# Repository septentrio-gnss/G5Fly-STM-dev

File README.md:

<div align="center">

# G5Fly STM

**Open-source Septentrio GNSS board for FPV drones.**

[Features](#why-g5fly-stm-on-your-drone) •
[Getting started](#getting-started-on-an-fpv-drone) •
[Antenna](#antenna) •
[Production](#production-and-manufacturing) •
[Design guide](DESIGN.md) •
[License](#license)

</div>

G5Fly STM puts a Septentrio Mosaic-G5 GNSS receiver on a 30.5 x 30.5 mm FPV stack board. It mounts directly in your drone's stack and connects to your ArduPilot flight controller over DroneCAN or UART. An STM32G473 runs the AP_Periph firmware on board.

This repository contains the hardware design (KiCad), the production files and the AP_Periph firmware configuration.

Author: <a href="https://github.com/TheophileRaimbault">Théophile Raimbault</a><br>
Contributors: <a href="https://github.com/amelaille">Amélie Hidalgo Peryllous</a>, <a href="https://github.com/robbe2000martens">Robbe Martens</a><br>
Maintainer: Septentrio GNSS GitHub user <githubuser@septentrio.com><br>
License: <a href="https://creativecommons.org/licenses/by-sa/4.0/">Creative Commons Attribution-ShareAlike 4.0</a> and <a href="https://www.oshwa.org/definition/">Open Source Hardware</a><br>

<table>
  <tr>
    <td align="center"><br><strong>Top</strong></td>
    <td align="center"><br><strong>Bottom</strong></td>
  </tr>
</table>

<p align="center">
  <br>
  <em>G5Fly STM mounted in a 30.5 x 30.5 mm FPV stack</em>
</p>

<details>
<summary><strong>Table of contents</strong></summary>

- [Why G5Fly STM on your drone?](#why-g5fly-stm-on-your-drone)
- [Who is this repository for?](#who-is-this-repository-for)
- [Getting started on an FPV drone](#getting-started-on-an-fpv-drone)
  - [Interfaces](#interfaces)
- [Antenna](#antenna)
  - [Recommended antennas](#recommended-antennas)
- [Also compatible with the NXP MR-MCXN-T1 hub](#also-compatible-with-the-nxp-mr-mcxn-t1-hub)
- [Production and manufacturing](#production-and-manufacturing)
  - [JLCPCB requirements](#jlcpcb-requirements)
- [For designers and contributors](#for-designers-and-contributors)
- [Repository structure](#repository-structure)
- [License](#license)

</details>

## Why G5Fly STM on your drone?

- **Fits your FPV stack**: 30.5 x 30.5 mm mounting pattern, stacks directly with standard flight controllers and ESCs
- **Septentrio Mosaic-G5 accuracy**: multi-constellation, multi-frequency GNSS
- **Plug-and-play with ArduPilot**: AP_Periph node with DroneCAN support
- **Drone-standard connectors**: JST-GH connectors for DroneCAN, UART and I2C
- **Flexible antenna power**: 3.3 V or 5 V active antenna supply, selected with a jumper
- **Fully open source**: schematics, PCB, BOM and firmware configuration

## Who is this repository for?

- **Drone builders** who want to buy, assemble or fly the board as-is: start with the sections below.
- **Designers** who want to understand the hardware or make a custom version: go to [DESIGN.md](DESIGN.md).

## Getting started on an FPV drone

1. **Get a board**: build it from the production files in [hardware/versions/v1/kicad/production](hardware/versions/v1/kicad/production/) (see [Production and manufacturing](#production-and-manufacturing)).
2. **Set the antenna voltage**: solder `JP1` according to your antenna (see [Antenna](#antenna)).
3. **Flash the firmware**: build and flash AP_Periph using the configuration in [firmware](firmware/).
4. **Mount it in the stack**: install the board on the 30.5 x 30.5 mm pattern.
5. **Wire it to the flight controller**: use DroneCAN (recommended) or UART, then power it from the 5 V supply of the stack or via USB on the bench.
6. **Configure ArduPilot**: enable the DroneCAN GPS in Mission Planner (see [firmware/README.md](firmware/README.md)).
7. **Check before flying**: verify the status LEDs and wait for a valid GNSS fix outdoors.

### Interfaces

- **DroneCAN**: recommended link to the flight controller
- **UART**: direct serial link to the flight controller or a companion computer
- **I2C**: for external sensors
- **USB**: power and configuration on the bench
- **Reset input and status LEDs**

## Antenna

- Use an active antenna only with the voltage specified by the antenna manufacturer.
- Check the antenna connector and the `JP1` configuration before powering the board.
- On the drone, route the antenna cable away from the VTX, ESCs and motor wires, and mount the antenna with a clear view of the sky.

<div style="background-color:#ffebee; border-left:5px solid #c62828; padding:10px; border-radius:5px; margin:10px 0;">
  <strong>Warning:</strong> Solder <code>JP1</code> before using an active antenna. If the jumper is left open, the <code>VANT</code> net is not powered and the antenna may not work, causing a significant loss of GNSS performance. Select only one voltage according to the antenna datasheet.
</div>

<table>
  <tr>
    <td align="center"><br><strong>3.3 V antenna</strong><br>Connect <code>VANT</code> to <code>+3.3V_RF</code>.</td>
    <td align="center"><br><strong>5 V antenna</strong><br>Connect <code>VANT</code> to <code>+5V</code>.</td>
  </tr>
</table>

### Recommended antennas

- D-Helix HX-CHX600A
- D-Helix HX-CH7609A
- Calian HC990EXF

An SMA-to-MMCX adapter is often needed to connect these antennas to the board.

## Also compatible with the NXP MR-MCXN-T1 hub

G5Fly STM is designed for FPV drones first, but it also works with the NXP MR-MCXN-T1 hub through its DF40 connector.

<table>
  <tr>
    <td align="center"><br><strong>MR-MCXN-T1 housing</strong></td>
    <td align="center"><br><strong>DF40 connector</strong></td>
  </tr>
</table>

The DF40 connector carries the GNSS UART, the PPS and Event A signals, and the 5 V supply from the hub.

To get started on the hub, see the [G5Fly NXP repository](https://github.com/septentrio-gnss/G5Fly-NXP). It provides a Zephyr test application for the MR-MCXN-T1 that reads the GNSS position over NMEA, measures the PPS, and sends Event A pulses.

For an overview of the hardware and software integration, see the [MR-MCXN-T1 integration slides](resources/mr-mcxn-t1/NXP%20integration%20HW-FW.pdf).

## Production and manufacturing

For a production build without hardware changes:

- Use the KiCad project and manufacturing files in [hardware/versions/v1/kicad](hardware/versions/v1/kicad/).
- Provide the manufacturer with the schematic, PCB files, BOM and CPL.
- Check the antenna connector type, jumper configuration and power options before assembly.

### JLCPCB requirements

- Keep the default KiCad PCB setup and its calculated impedance settings.
- Manufacture the board as a 6-layer PCB.
- `PCB Requirement: User.1 layer should be used as the V-cut guide layer.`
- Follow the PCB design rules in [hardware/common/design_rules/design-rules.md](hardware/common/design_rules/design-rules.md).
- Use the [G5Fly_STM_v1 production archive](hardware/versions/v1/kicad/production/G5Fly_STM_v1.zip), prepared for JLCPCB.

## For designers and contributors

The detailed hardware design guide is in [DESIGN.md](DESIGN.md). It covers:

- Overall architecture and major blocks
- Component selection and board organization
- How to create a custom derivative board
- Manufacturing and validation recommendations
- AP_Periph firmware configuration and DroneCAN bring-up

Useful resources:

- STM32 schematic: [resources/schematics/G5FLY_STM_schematics.pdf](resources/schematics/G5FLY_STM_schematics.pdf)
- Block diagram: [resources/schematics/G5Fly_STM32_drawio.png](resources/schematics/G5Fly_STM32_drawio.png)
- Contribution rules: [GUIDELINES.md](GUIDELINES.md) and [VERSIONING.md](VERSIONING.md)

## Repository structure

- [hardware](hardware): KiCad projects, libraries, 3D models, design rules and production files
- [firmware](firmware): AP_Periph configuration (`hwdef.dat`, `defaults.parm`)
- [resources](resources): photos, marketing visuals, schematics and MR-MCXN-T1 integration documents

## License

The G5Fly hardware design files (schematics, PCB layouts, production files) and documentation are released under the [Creative Commons Attribution-ShareAlike 4.0 International License](https://creativecommons.org/licenses/by-sa/4.0/) (CC BY-SA 4.0). See the [LICENSE](LICENSE) file for the full text.

You are free to share and adapt this design, including for commercial purposes, as long as you:
- **give appropriate credit** to Septentrio and the original authors,
- **indicate if changes were made**,
- **distribute your derivatives under the same license**.

G5Fly is open-source hardware and follows the [Open Source Hardware Definition](https://www.oshwa.org/definition/).

<p align="right"><a href="#g5fly-stm">Back to top ↑</a></p>

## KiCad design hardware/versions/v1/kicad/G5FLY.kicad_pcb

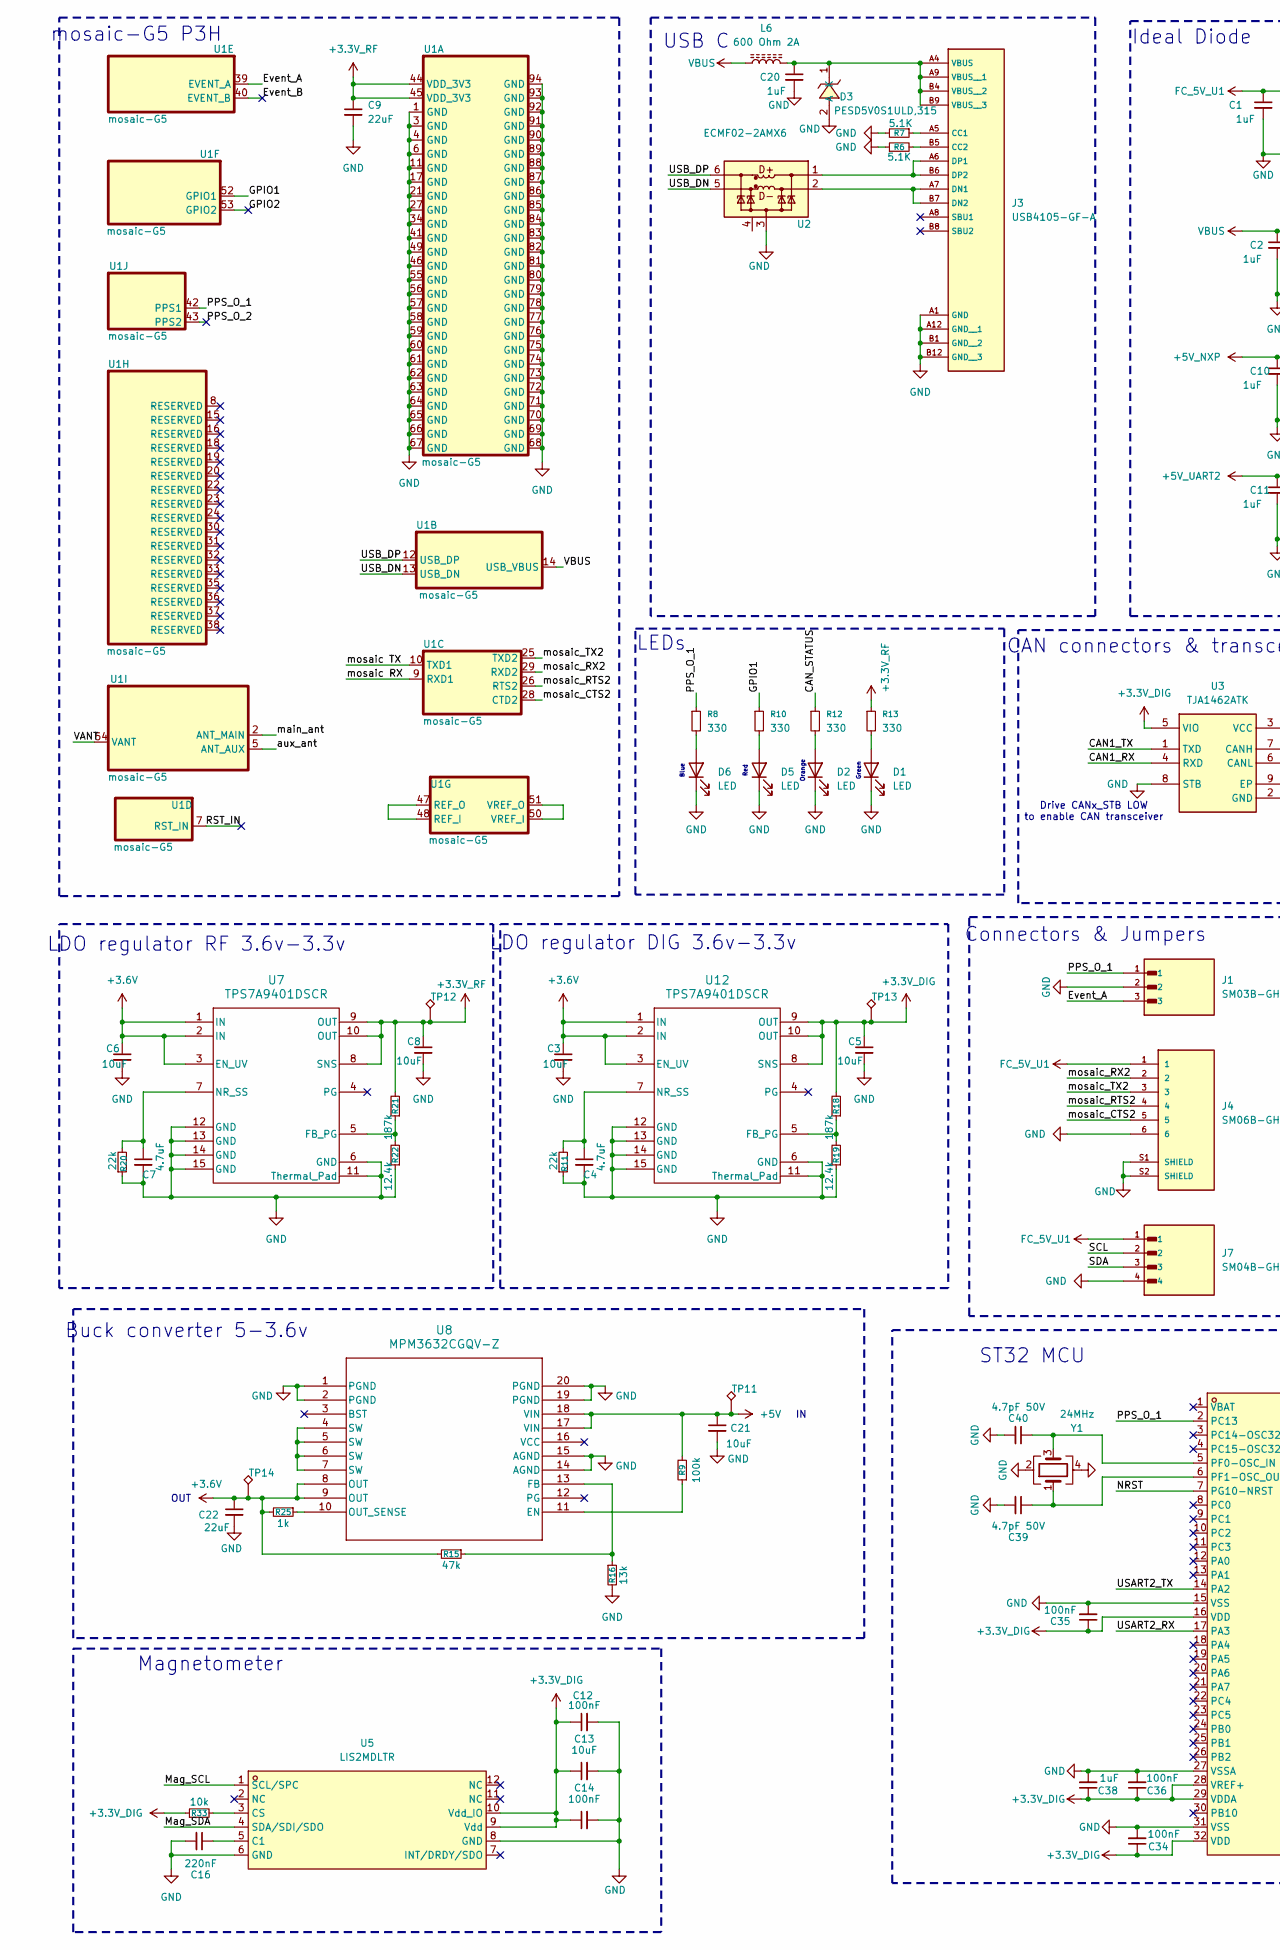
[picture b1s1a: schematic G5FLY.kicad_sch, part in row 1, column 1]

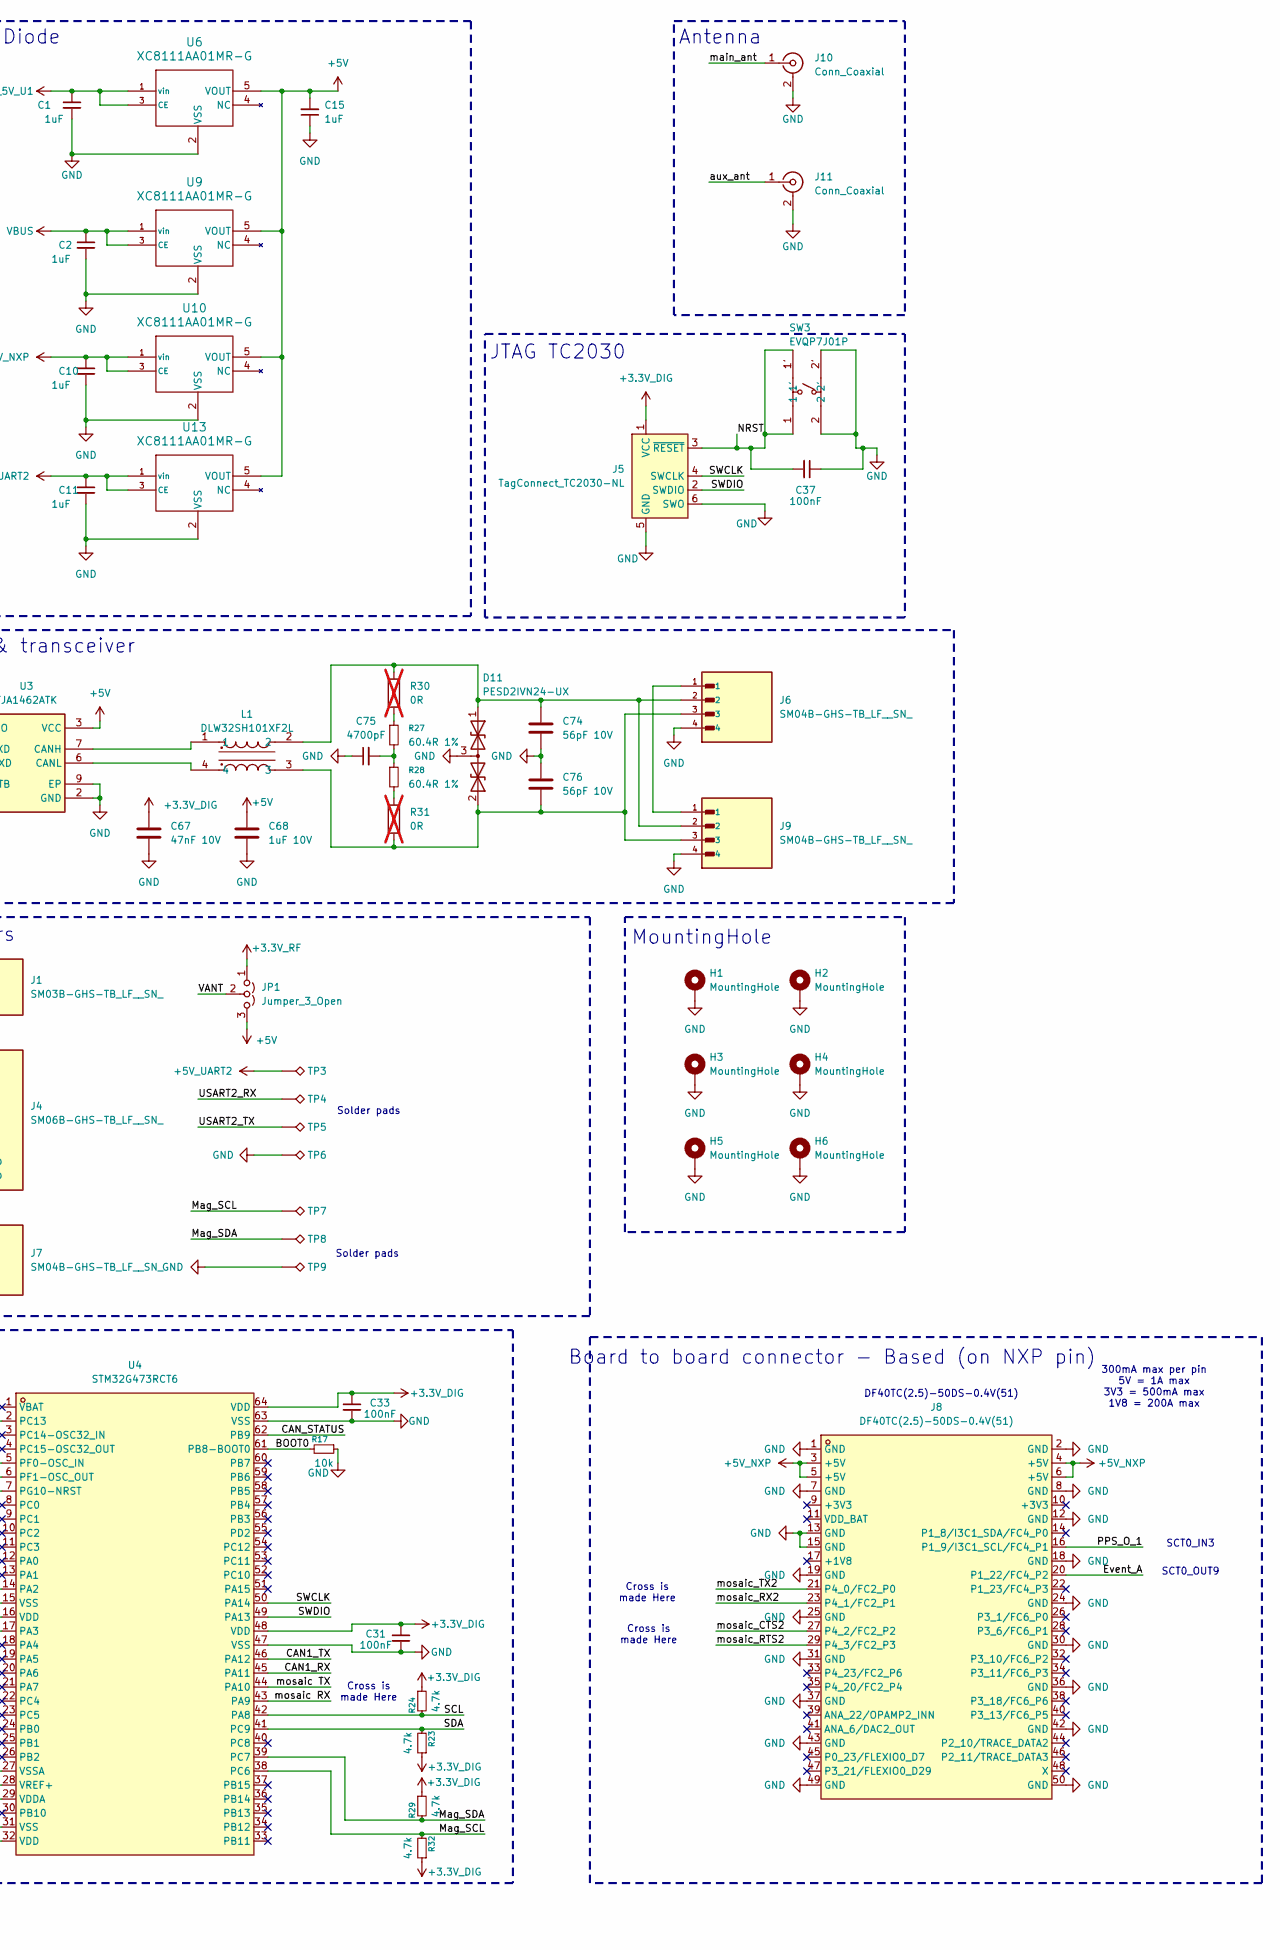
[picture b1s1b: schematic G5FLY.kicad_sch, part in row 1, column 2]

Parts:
C1, C2, C10, C11, C15, C20, C38: 1uF; C_0402_1005Metric
C3, C5, C6, C8, C21: 10uF; C_0603_1608Metric
C4: 4.7uF; C_0402_1005Metric
C7: 4.7uF; C_0603_1608Metric
C9, C22: 22uF; C_0805_2012Metric
C12, C14, C31, C33, C34, C35, C36, C37: 100nF; C_0402_1005Metric
C13: 10uF; C_0402_1005Metric
C16: 220nF; C_0402_1005Metric
C39, C40: 4.7pF 50V; C_0402_1005Metric
C67: 47nF 10V; C_0402_1005Metric; JLCPCB C77012
C68: 1uF 10V; C_0402_1005Metric; JLCPCB C528974
C74, C76: 56pF 10V; C_0402_1005Metric; JLCPCB C107007
C75: 4700pF
D1, D2, D5, D6: LED; LED_0402_1005Metric
D3: PESD5V0S1ULD,315; SOD-882_L1.0-W0.6-RD; MPN PESD5V0S1ULD,315; LCSC Part C552570
D11: PESD2IVN24-UX; SOT-323_SC-70; JLCPCB C552496
H1, H2, H3, H4, H5, H6: MountingHole; MountingHole_3.2mm_M3_DIN965_Pad
J1: SM03B-GHS-TB_LF__SN_; JST_SM03B-GHS-TB_LF__SN_
J3: USB4105-GF-A; USB_C_Receptacle_GCT_USB4105-xx-A_16P_TopMnt_Horizontal
J4: SM06B-GHS-TB_LF__SN_; JST_SM06B-GHS-TB_LF__SN_; PARTREV N/A
J5: TagConnect_TC2030-NL; Tag-Connect_TC2030-IDC-NL_2x03_P1.27mm_Vertical
J6, J7, J9: SM04B-GHS-TB_LF__SN_; JST_SM04B-GHS-TB_LF__SN_
J8: DF40TC(2.5)-50DS-0.4V(51); CONN-SMD_DF40C-50DS-0.4V51; MPN DF40C-50DS-0.4V(51); LCSC Part C424646
J10, J11: Conn_Coaxial; SAMTEC_MMCX-J-P-H-RA-TH1
JP1: Jumper_3_Open; SolderJumper-3_P1.3mm_Open_Pad1.0x1.5mm_NumberLabels
L1: DLW32SH101XF2L; FILTER-SMD_4P-L3.2-W2.5-BL_DLW32SH510XK2L; MPN DLW32SH101XF2L; LCSC Part C1857795
L6: 600 Ohm 2A; L_0603_1608Metric; DigiKey 445-MPZ2012S601ATD25CT-ND
R6, R7: 5.1K; R_0402_1005Metric
R8, R10, R12, R13: 330; R_0402_1005Metric
R9: 100k; R_0402_1005Metric
R11, R20: 22k; R_0402_1005Metric
R15: 47k; R_0402_1005Metric
R16: 13k; R_0402_1005Metric
R17, R33: 10k; R_0402_1005Metric
R18, R21: 187k; R_0402_1005Metric
R19, R22: 12.4k; R_0402_1005Metric
R23, R24, R29, R32: 4.7k; R_0402_1005Metric
R25: 1k; R_0402_1005Metric
R27, R28: 60.4R 1%; R_0402_1005Metric
R30, R31: 0R; R_0603_1608Metric; DigiKey 541-60.4SCT-ND; not fitted
SW3: EVQP7J01P; SW-SMD_EVQP7J01P; MPN EVQP7J01P; LCSC Part C2828254
TP3, TP4, TP5, TP6, TP7, TP8, TP9: TestPoint_Alt; TestPoint_Pad_1.5x1.5mm
TP11, TP12, TP13, TP14: TestPoint_Alt; TestPoint_Pad_D1.0mm
U1: mosaic-G5; LGA54_MOSAIC-MINI_SEP
U2: ECMF02-2AMX6; ST_UQFN-6L_1.5x1.7mm_P0.5mm
U3: TJA1462ATK; SON65P300X300X100-9N-D; JLCPCB C3229259
U4: STM32G473RCT6; LQFP-64_L10.0-W10.0-P0.50-LS12.0-BL; MPN STM32G473RCT6; LCSC Part C529361
U5: LIS2MDLTR; VLGA-12_L2.0-W2.0-P0.50-BL; MPN LIS2MDLTR; LCSC Part C919695
U6, U9, U10, U13: XC8111AA01MR-G; IC_XC8111AA01MR-G
U7, U12: TPS7A9401DSCR; DSC0010J-MFG
U8: MPM3632CGQV-Z; QFN3p0x5p0x1p6_MPM3632C_MNP
Y1: 24MHz; Crystal_SMD_2016-4Pin_2.0x1.6mm; DigiKey 1923-830108212309CT-ND

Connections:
+3.3V_DIG: C5.1, C12.1, C13.1, C14.1, C31.1, C33.1, C34.1, C35.1, C36.1, C38.1, C67.1, J5.1 (VCC), R18.2, R23.1, R24.1, R29.1, R32.1, R33.1, TP13.1 (1_1), U3.5 (VIO), U4.16 (VDD), U4.28 (VREF+), U4.29 (VDDA), U4.32 (VDD), U4.48 (VDD), U4.64 (VDD), U5.9 (Vdd), U5.10 (Vdd_IO), U12.8 (SNS), U12.9 (OUT), U12.10 (OUT)
+3.3V_RF: C8.1, C9.1, JP1.1 (A), R13.1, R21.2, TP12.1 (1_1), U1.44 (VDD_3V3), U1.45 (VDD_3V3), U7.8 (SNS), U7.9 (OUT), U7.10 (OUT)
+3.6V: C3.1, C6.1, C22.1, R15.2, R25.2, TP14.1 (1_1), U7.1 (IN), U7.2 (IN), U7.3 (EN_UV), U8.8 (OUT), U8.9 (OUT), U12.1 (IN), U12.2 (IN), U12.3 (EN_UV)
+5V: C15.2, C21.1, C68.1, JP1.3 (B), R9.2, TP11.1 (1_1), U3.3 (VCC), U6.5 (VOUT), U8.17 (VIN), U8.18 (VIN), U9.5 (VOUT), U10.5 (VOUT), U13.5 (VOUT)
+5V_NXP: C10.1, J8.3 (+5V), J8.4 (+5V), J8.5 (+5V), J8.6 (+5V), U10.1 (vin), U10.3 (CE)
+5V_UART2: C11.1, TP3.1 (1_1), U13.1 (vin), U13.3 (CE)
/BOOT0: R17.2, U4.61 (PB8-BOOT0)
/CAN1_RX: U3.4 (RXD), U4.45 (PA11)
/CAN1_TX: U3.1 (TXD), U4.46 (PA12)
/CAN_STATUS: R12.1, U4.62 (PB9)
/Event_A: J1.3, J8.20 (P1_22/FC4_P2), U1.39 (EVENT_A)
/Event_B: U1.40 (EVENT_B)
/GPIO1: R10.1, U1.52 (GPIO1)
/GPIO2: U1.53 (GPIO2)
/Mag_SCL: R32.2, TP7.1 (1_1), U4.38 (PC6), U5.1 (SCL/SPC)
/Mag_SDA: R29.2, TP8.1 (1_1), U4.39 (PC7), U5.4 (SDA/SDI/SDO)
/NRST: C37.2, J5.3 (~RESET), SW3.1, SW3.1', U4.7 (PG10-NRST)
/PPS_O_1: J1.1, J8.16 (P1_9/I3C1_SCL/FC4_P1), R8.1, U1.42 (PPS1), U4.2 (PC13)
/PPS_O_2: U1.43 (PPS2)
/RST_IN: U1.7 (RST_IN)
/SCL: J7.2, R24.2, U4.42 (PA8)
/SDA: J7.3, R23.2, U4.41 (PC9)
/SWCLK: J5.4 (SWCLK), U4.50 (PA14)
/SWDIO: J5.2 (SWDIO), U4.49 (PA13)
/USART2_RX: TP4.1 (1_1), U4.17 (PA3)
/USART2_TX: TP5.1 (1_1), U4.14 (PA2)
/USB_DN: U1.13 (USB_DN), U2.5 (D-_out)
/USB_DP: U1.12 (USB_DP), U2.6 (D+_out)
/VANT: JP1.2 (C), U1.54 (VANT)
/aux_ant: J11.1 (In), U1.5 (ANT_AUX)
/main_ant: J10.1 (In), U1.2 (ANT_MAIN)
/mosaic RX: U1.9 (RXD1), U4.43 (PA9)
/mosaic TX: U1.10 (TXD1), U4.44 (PA10)
/mosaic_CTS2: J4.5, J8.27 (P4_2/FC2_P2), U1.28 (CTD2)
/mosaic_RTS2: J4.4, J8.29 (P4_3/FC2_P3), U1.26 (RTS2)
/mosaic_RX2: J4.2, J8.23 (P4_1/FC2_P1), U1.29 (RXD2)
/mosaic_TX2: J4.3, J8.21 (P4_0/FC2_P0), U1.25 (TXD2)
FC_5V_U1: C1.1, J4.1, J7.1, U6.1 (vin), U6.3 (CE)
GND: C1.2, C2.2, C3.2, C4.2, C5.2, C6.2, C7.2, C8.2, C9.2, C10.2, C11.2, C12.2, C13.2, C14.2, C15.1, C16.2, C20.2, C21.2, C22.2, C31.2, C33.2, C34.2, C35.2, C36.2, C37.1, C38.2, C39.2, C40.2, C67.2, C68.2, C74.2, C75.1, C76.1, D1.1 (K), D2.1 (K), D3.2 (A), D5.1 (K), D6.1 (K), D11.3 (common), H1.1 (1_1), H2.1 (1_1), H3.1 (1_1), H4.1 (1_1), H5.1 (1_1), H6.1 (1_1), J1.2, J3.A1 (GND), J3.A12 (GND__1), J3.B1 (GND__2), J3.B12 (GND__3), J4.6, J4.S1 (SHIELD), J4.S2 (SHIELD), J5.5 (GND), J5.6 (SWO), J6.4, J7.4, J8.1 (GND), J8.2 (GND), J8.7 (GND), J8.8 (GND), J8.12 (GND), J8.13 (GND), J8.15 (GND), J8.18 (GND), J8.19 (GND), J8.24 (GND), J8.25 (GND), J8.30 (GND), J8.31 (GND), J8.36 (GND), J8.37 (GND), J8.42 (GND), J8.43 (GND), J8.49 (GND), J8.50 (GND), J9.4, J10.2 (Ext), J11.2 (Ext), R6.1, R7.2, R11.1, R16.2, R17.1, R19.1, R20.1, R22.1, SW3.2, SW3.2', TP6.1 (1_1), TP9.1 (1_1), U1.1 (GND), U1.3 (GND), U1.4 (GND), U1.6 (GND), U1.11 (GND), U1.17 (GND), U1.21 (GND), U1.27 (GND), U1.34 (GND), U1.41 (GND), U1.46 (GND), U1.49 (GND), U1.55 (GND), U1.56 (GND), U1.57 (GND), U1.58 (GND), U1.59 (GND), U1.60 (GND), U1.61 (GND), U1.62 (GND), U1.63 (GND), U1.64 (GND), U1.65 (GND), U1.66 (GND), U1.67 (GND), U1.68 (GND), U1.69 (GND), U1.70 (GND), U1.71 (GND), U1.72 (GND), U1.73 (GND), U1.74 (GND), U1.75 (GND), U1.76 (GND), U1.77 (GND), U1.78 (GND), U1.79 (GND), U1.80 (GND), U1.81 (GND), U1.82 (GND), U1.83 (GND), U1.84 (GND), U1.85 (GND), U1.86 (GND), U1.87 (GND), U1.88 (GND), U1.89 (GND), U1.90 (GND), U1.91 (GND), U1.92 (GND), U1.93 (GND), U1.94 (GND), U2.3 (GND), U3.2 (GND), U3.8 (STB), U3.9 (EP), U4.15 (VSS), U4.27 (VSSA), U4.31 (VSS), U4.47 (VSS), U4.63 (VSS), U5.6 (GND), U5.8 (GND), U6.2 (VSS), U7.6 (GND), U7.11 (Thermal_Pad), U7.12 (GND), U7.13 (GND), U7.14 (GND), U7.15 (GND), U8.1 (PGND), U8.2 (PGND), U8.14 (AGND), U8.15 (AGND), U8.19 (PGND), U8.20 (PGND), U9.2 (VSS), U10.2 (VSS), U12.6 (GND), U12.11 (Thermal_Pad), U12.12 (GND), U12.13 (GND), U12.14 (GND), U12.15 (GND), U13.2 (VSS), Y1.2, Y1.4
unnamed: C75.2, R27.2, R28.1
unnamed: D1.2 (A), R13.2
unnamed: D2.2 (A), R12.2
unnamed: C20.1, D3.1 (K), J3.A4 (VBUS), J3.A9 (VBUS__1), J3.B4 (VBUS__2), J3.B9 (VBUS__3), L6.2
unnamed: D5.2 (A), R10.2
unnamed: D6.2 (A), R8.2
unnamed: C74.1, D11.1 (A1), J6.2, J9.2, L1.2, R30.1
unnamed: C76.2, D11.2 (A2), J6.3, J9.3, L1.3, R31.2
unnamed: J3.A5 (CC1), R7.1
unnamed: J3.B5 (CC2), R6.2
unnamed: J3.A7 (DN1), J3.B7 (DN2), U2.2 (D-_in)
unnamed: J3.A6 (DP1), J3.B6 (DP2), U2.1 (D+_in)
unnamed: J6.1, J9.1
unnamed: R27.1, R30.2
unnamed: R28.2, R31.1
unnamed: U1.47 (REF_O), U1.48 (REF_I)
unnamed: U1.50 (VREF_I), U1.51 (VREF_O)
unnamed: L1.1, U3.7 (CANH)
unnamed: L1.4, U3.6 (CANL)
unnamed: C40.1, U4.5 (PF0-OSC_IN), Y1.3
unnamed: C39.1, U4.6 (PF1-OSC_OUT), Y1.1
unnamed: C16.1, U5.5 (C1)
unnamed: R33.2, U5.3 (CS)
unnamed: R21.1, R22.2, U7.5 (FB_PG)
unnamed: C7.1, R20.2, U7.7 (NR_SS)
unnamed: R9.1, U8.11 (EN)
unnamed: R15.1, R16.1, U8.13 (FB)
unnamed: R25.1, U8.10 (OUT_SENSE)
unnamed: U8.4 (SW), U8.5 (SW), U8.6 (SW), U8.7 (SW)
unnamed: R18.1, R19.2, U12.5 (FB_PG)
unnamed: C4.1, R11.2, U12.7 (NR_SS)
VBUS: C2.1, L6.1, U1.14 (USB_VBUS), U9.1 (vin), U9.3 (CE)

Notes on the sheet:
DF40TC(2.5)-50DS-0.4V(51)
CAN connectors & transceiver
ST32 MCU
Connectors & Jumpers
Cross is made Here
LDO regulator DIG 3.6v-3.3v
Solder pads
mosaic-G5 P3H
Board to board connector - Based (on NXP pin)
LDO regulator RF 3.6v-3.3v
OUT
Red
Drive CANx_STB LOW to enable CAN transceiver
Buck converter 5-3.6v
Ideal Diode
Orange
USB C
300mA max per pin 5V = 1A max 3V3 = 500mA max 1V8 = 200A max
Green
SCT0_OUT9
Blue
Antenna
JTAG TC2030
LEDs
MountingHole
SCT0_IN3
Magnetometer

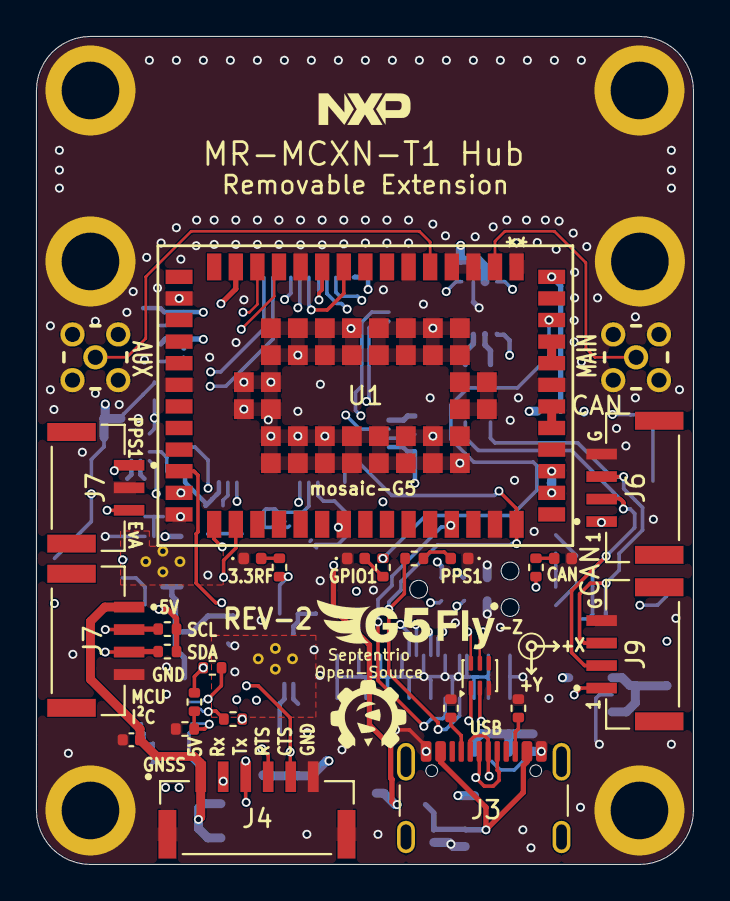
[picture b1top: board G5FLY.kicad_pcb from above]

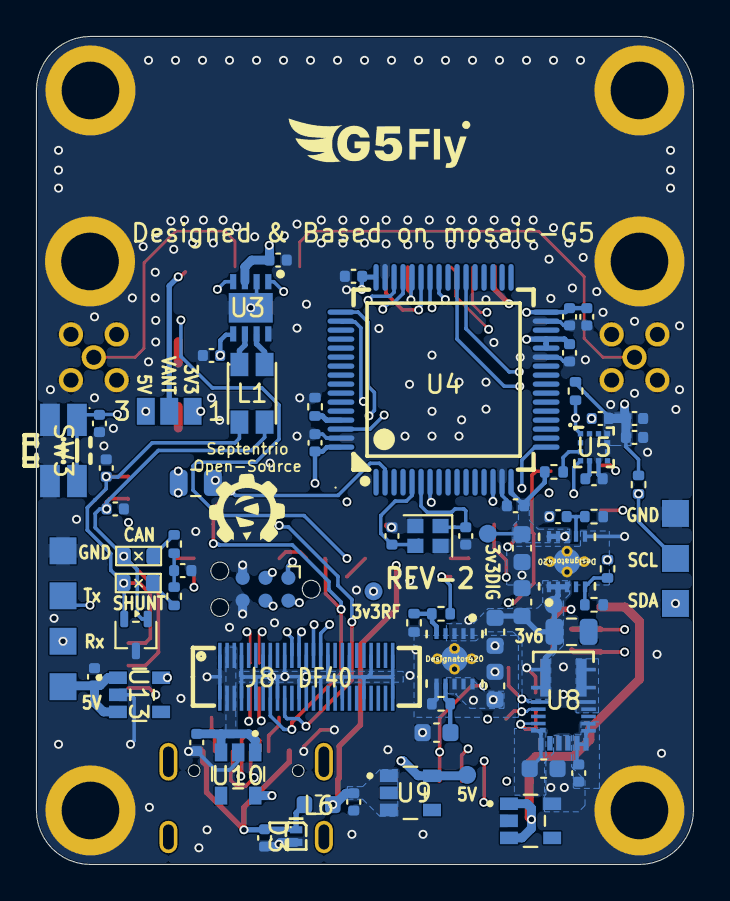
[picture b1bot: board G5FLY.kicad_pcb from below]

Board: 6 copper layers, 36.5 x 46.0 mm, 109 parts (76 on the bottom side), 67 nets.

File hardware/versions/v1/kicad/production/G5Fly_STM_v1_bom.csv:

Comment,Designator,Footprint,LCSC Part #,Quantity
1uF,"C1, C2, C10, C11, C15, C20, C38, C68",0402,C52923,8
10uF,"C3, C5, C6, C8, C21",0603,C19702,5
4.7uF,C4,0402,C23733,1
4.7uF,C7,0603,C19666,1
22uF,"C9, C22",0805,C45783,2
100nF,"C12, C14, C31, C33, C34, C35, C36, C37",0402,C1525,8
10uF,C13,0402,C15525,1
220nF,C16,0402,C16772,1
4.7pF 50V,"C39, C40",0402,C1569,2
47nF 10V,C67,0402,C82219,1
56pF 10V,"C74, C76",0402,C107007,2
4700pF,C75,0402,C1538,1
LED,"D1, D2, D5, D6",0402,C965793,4
"PESD5V0S1ULD,315",D3,SOD-882_L1.0-W0.6-RD,C85402,1
PESD2IVN24-UX,D11,SOT-323_SC-70,C552496,1
SM03B-GHS-TB_LF__SN_,J1,JST_SM03B-GHS-TB_LF__SN_,C514175,1
USB4105-GF-A,J3,USB_C_Receptacle_GCT_USB4105-xx-A_16P_TopMnt_Horizontal,C3020560,1
SM06B-GHS-TB_LF__SN_,J4,JST_SM06B-GHS-TB_LF__SN_,C51940119,1
SM04B-GHS-TB_LF__SN_,"J6, J7, J9",JST_SM04B-GHS-TB_LF__SN_,C51940118,3
DF40TC(2.5)-50DS-0.4V(51),J8,CONN-SMD_DF40C-50DS-0.4V51,C3644927,1
Conn_Coaxial,"J10, J11",SAMTEC_MMCX-J-P-H-RA-TH1,C2934607,2
DLW32SH101XF2L,L1,FILTER-SMD_4P-L3.2-W2.5-BL_DLW32SH510XK2L,C1857795,1
600 Ohm 2A,L6,0603,C668302,1
5.1K,"R6, R7",0402,C25905,2
330,"R8, R10, R12, R13",0402,C25104,4
100k,R9,0402,C25741,1
22k,"R11, R20",0402,C25768,2
47k,R15,0402,C25792,1
13k,R16,0402,C25754,1
10k,"R17, R33",0402,C25744,2
187k,"R18, R21",0402,C25761,2
12.4k,"R19, R22",0402,C11692,2
4.7k,"R23, R24, R29, R32",0402,C25900,4
1k,R25,0402,C11702,1
60.4R 1%,"R27, R28",0402,C60310,2
EVQP7J01P,SW3,SW-SMD_EVQP7J01P,C2828254,1
mosaic-G5,U1,LGA54_MOSAIC-MINI_SEP,,1
ECMF02-2AMX6,U2,ST_UQFN-6L_1.5x1.7mm_P0.5mm,C2651144,1
TJA1462ATK,U3,SON65P300X300X100-9N-D,C3229259,1
STM32G473RCT6,U4,LQFP-64_L10.0-W10.0-P0.50-LS12.0-BL,C529361,1
LIS2MDLTR,U5,VLGA-12_L2.0-W2.0-P0.50-BL,C919695,1
XC8111AA01MR-G,"U6, U9, U10, U13",IC_XC8111AA01MR-G,C3235548,4
TPS7A9401DSCR,"U7, U12",DSC0010J-MFG,C5220127,2
MPM3632CGQV-Z,U8,QFN3p0x5p0x1p6_MPM3632C_MNP,C3151646,1
24MHz,Y1,Crystal_SMD_2016-4Pin_2.0x1.6mm,C725986,1

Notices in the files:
README.md:
License: CC BY-SA 4.0
